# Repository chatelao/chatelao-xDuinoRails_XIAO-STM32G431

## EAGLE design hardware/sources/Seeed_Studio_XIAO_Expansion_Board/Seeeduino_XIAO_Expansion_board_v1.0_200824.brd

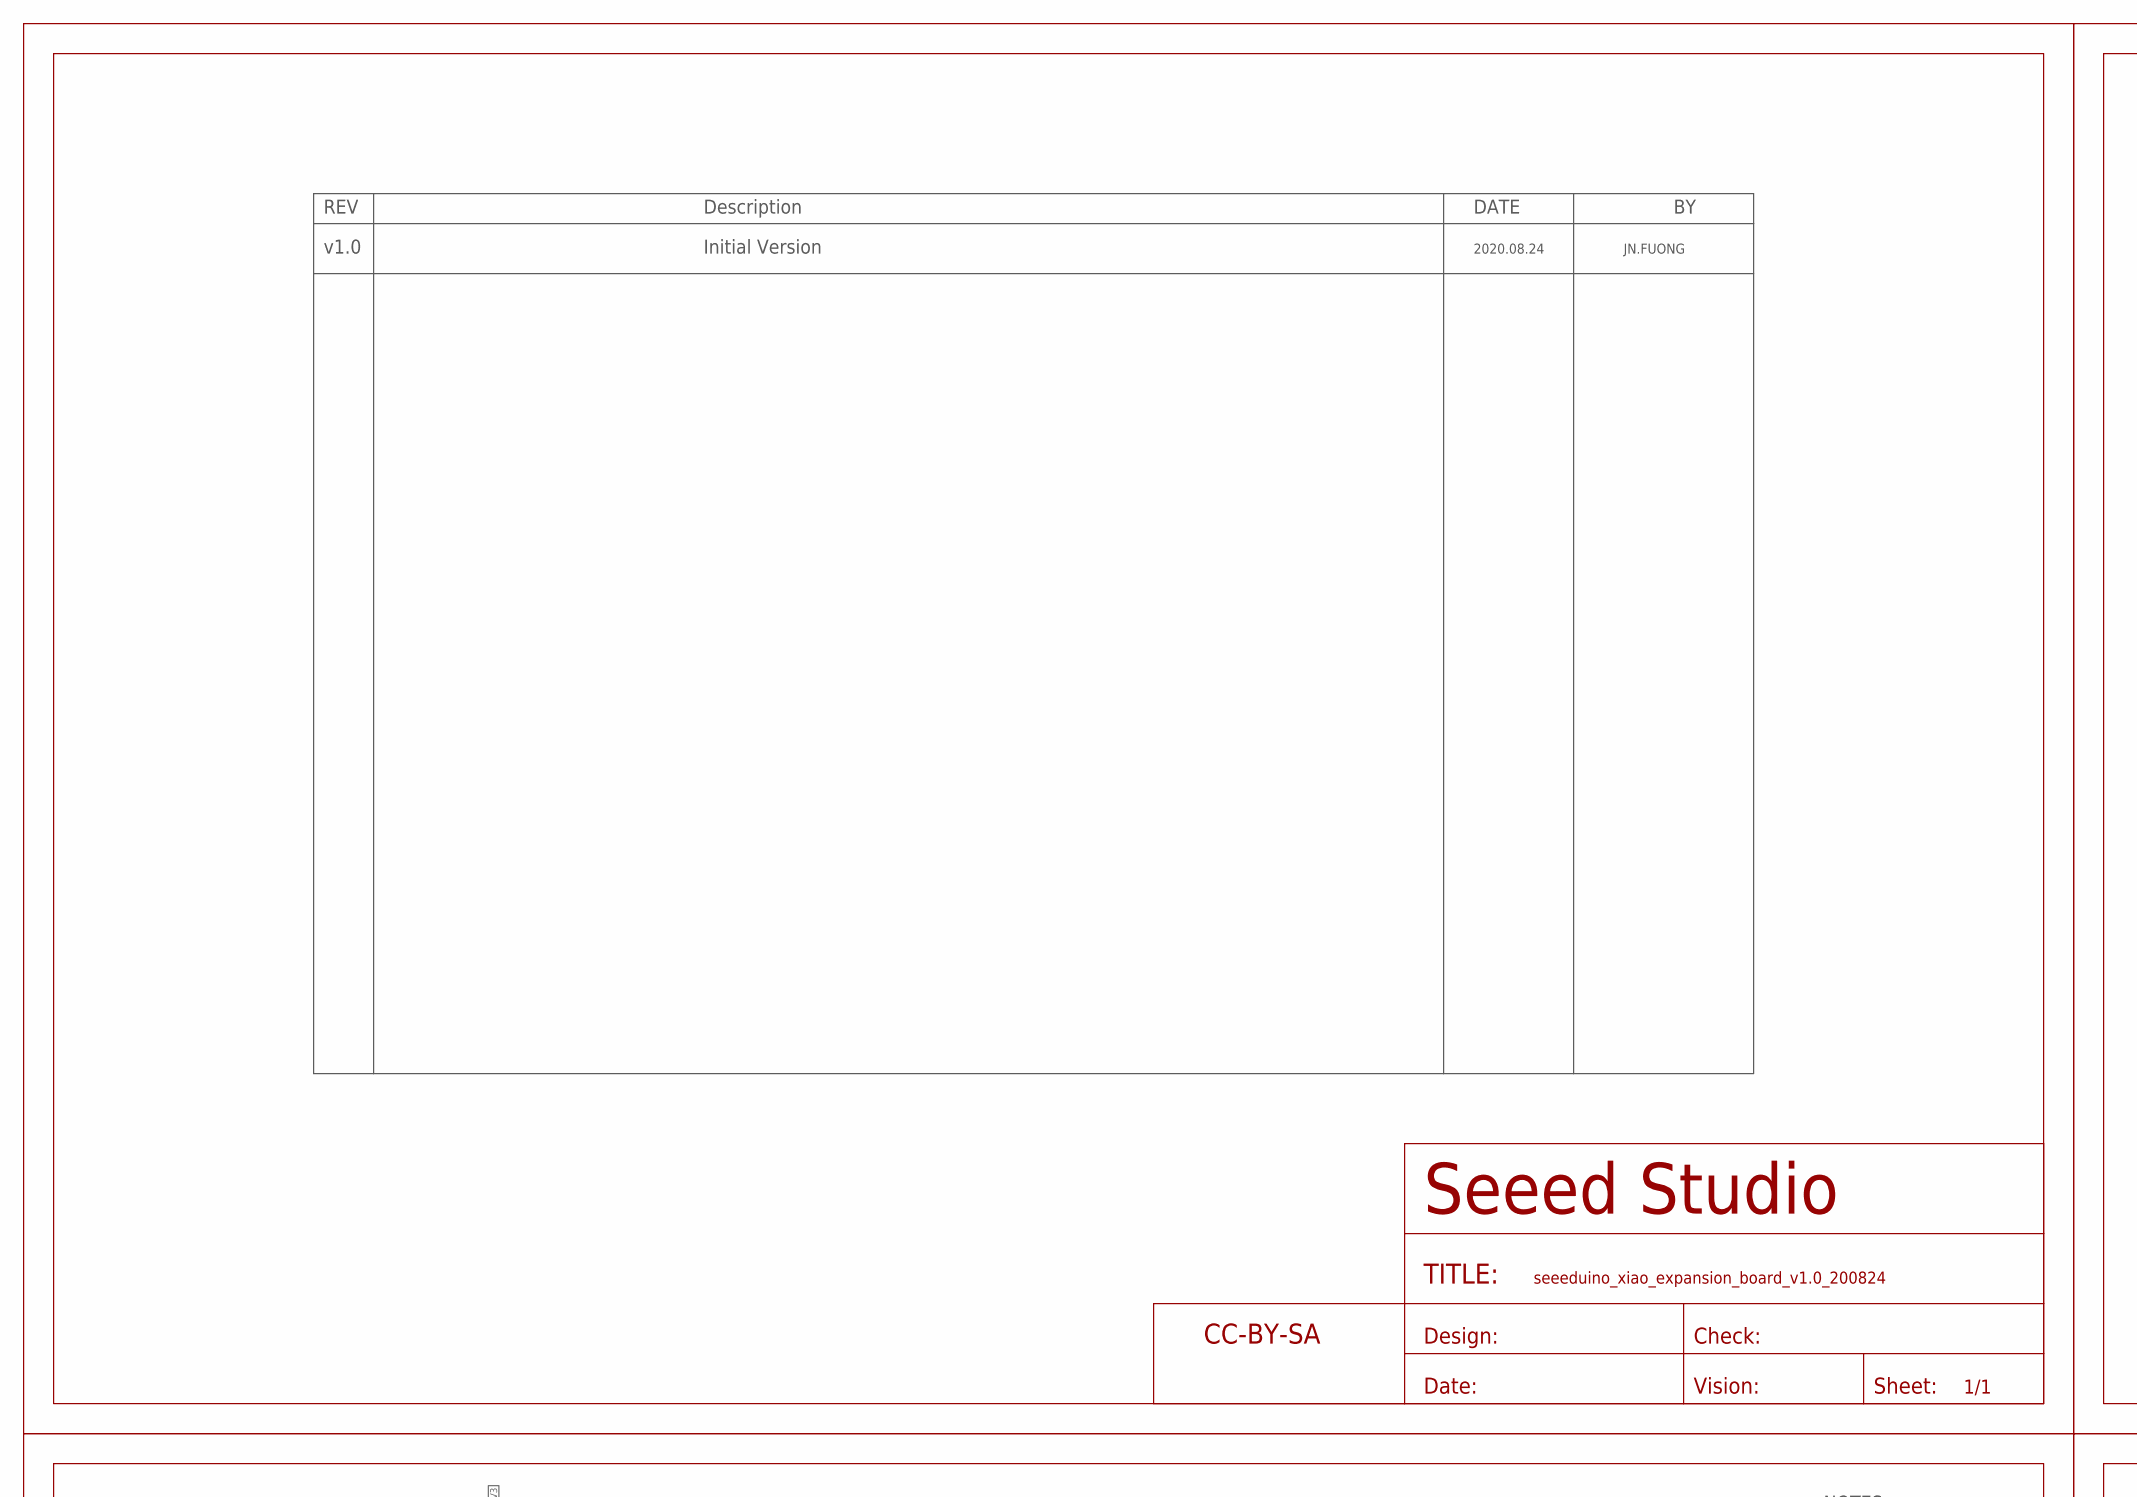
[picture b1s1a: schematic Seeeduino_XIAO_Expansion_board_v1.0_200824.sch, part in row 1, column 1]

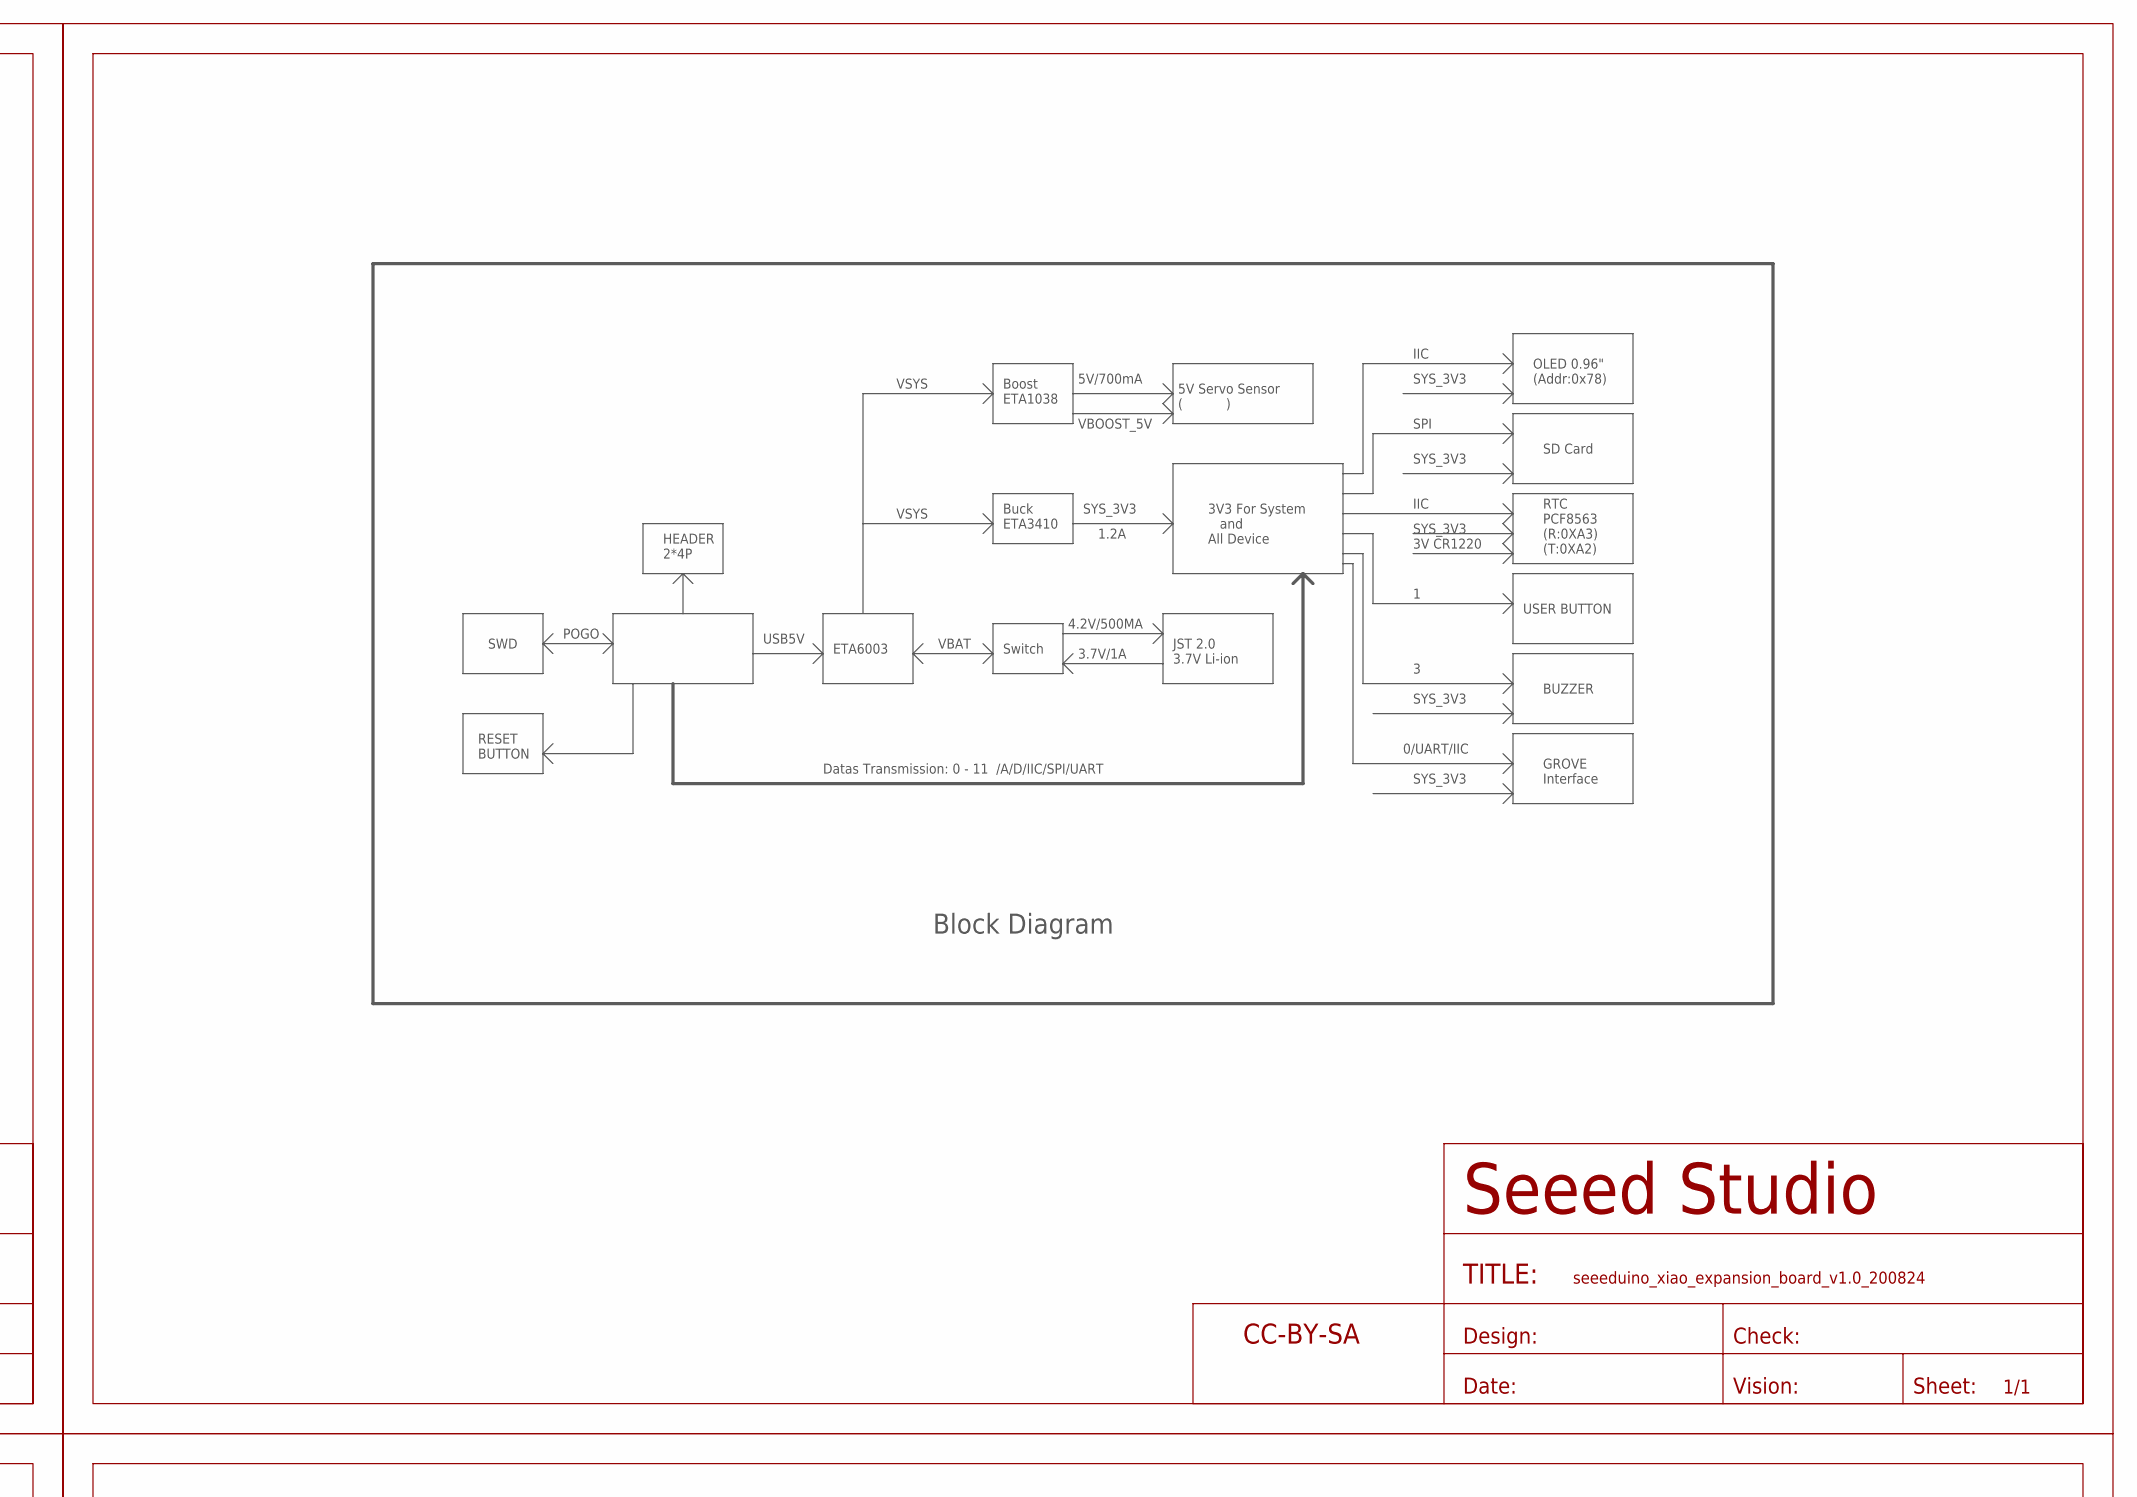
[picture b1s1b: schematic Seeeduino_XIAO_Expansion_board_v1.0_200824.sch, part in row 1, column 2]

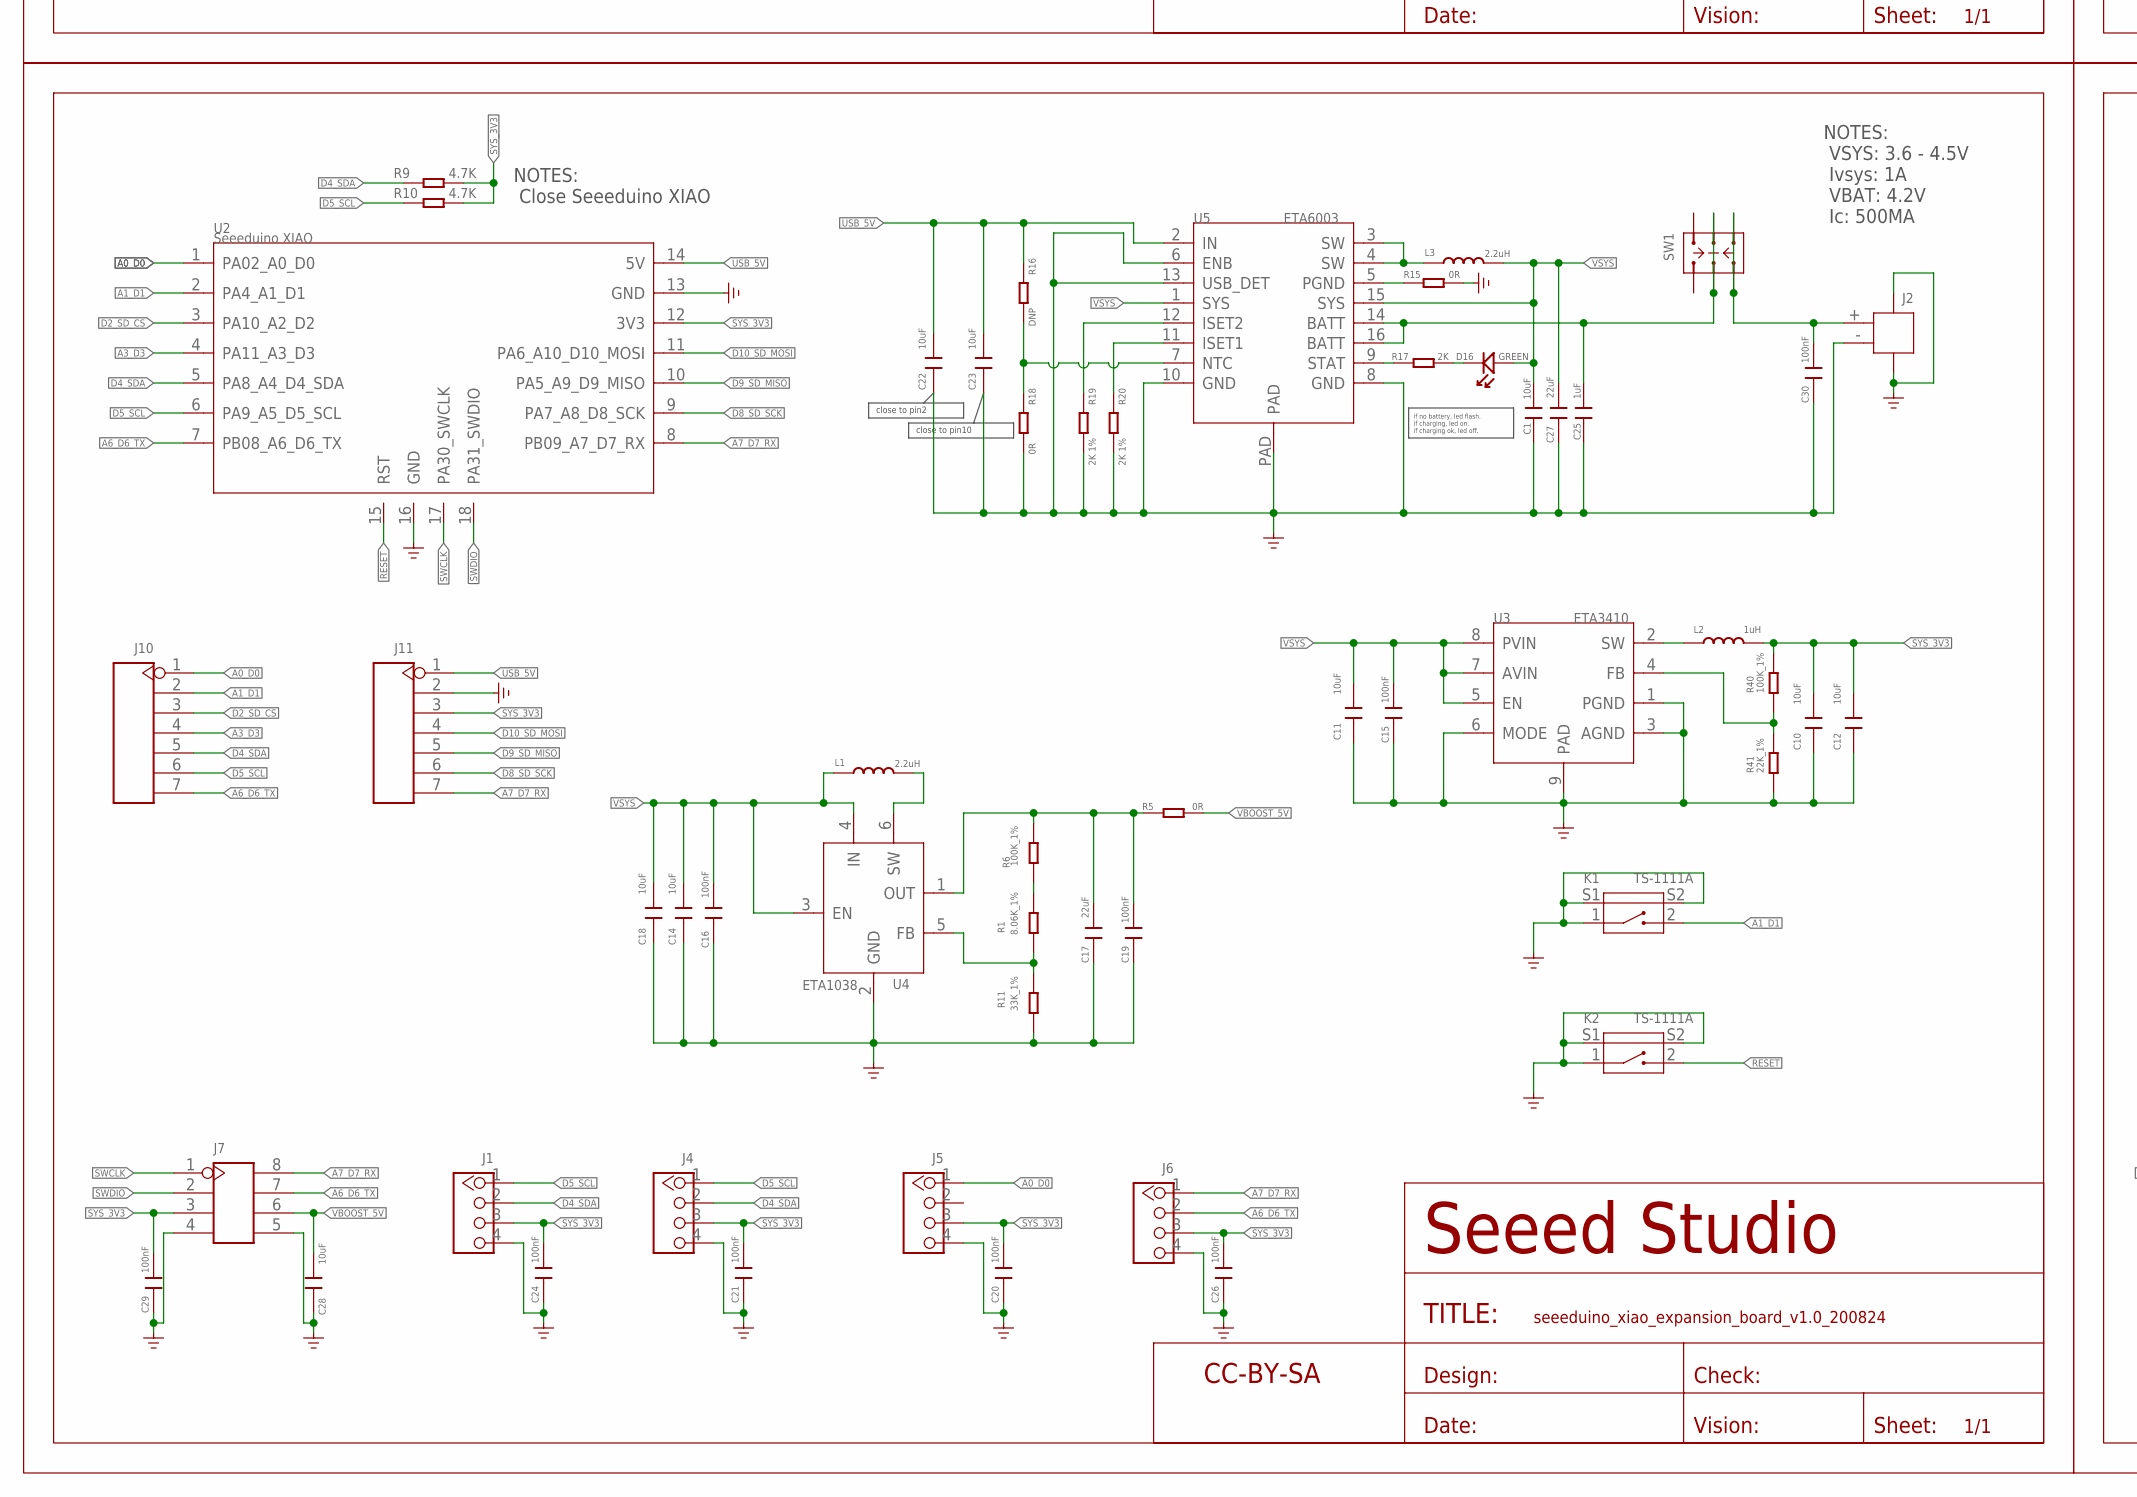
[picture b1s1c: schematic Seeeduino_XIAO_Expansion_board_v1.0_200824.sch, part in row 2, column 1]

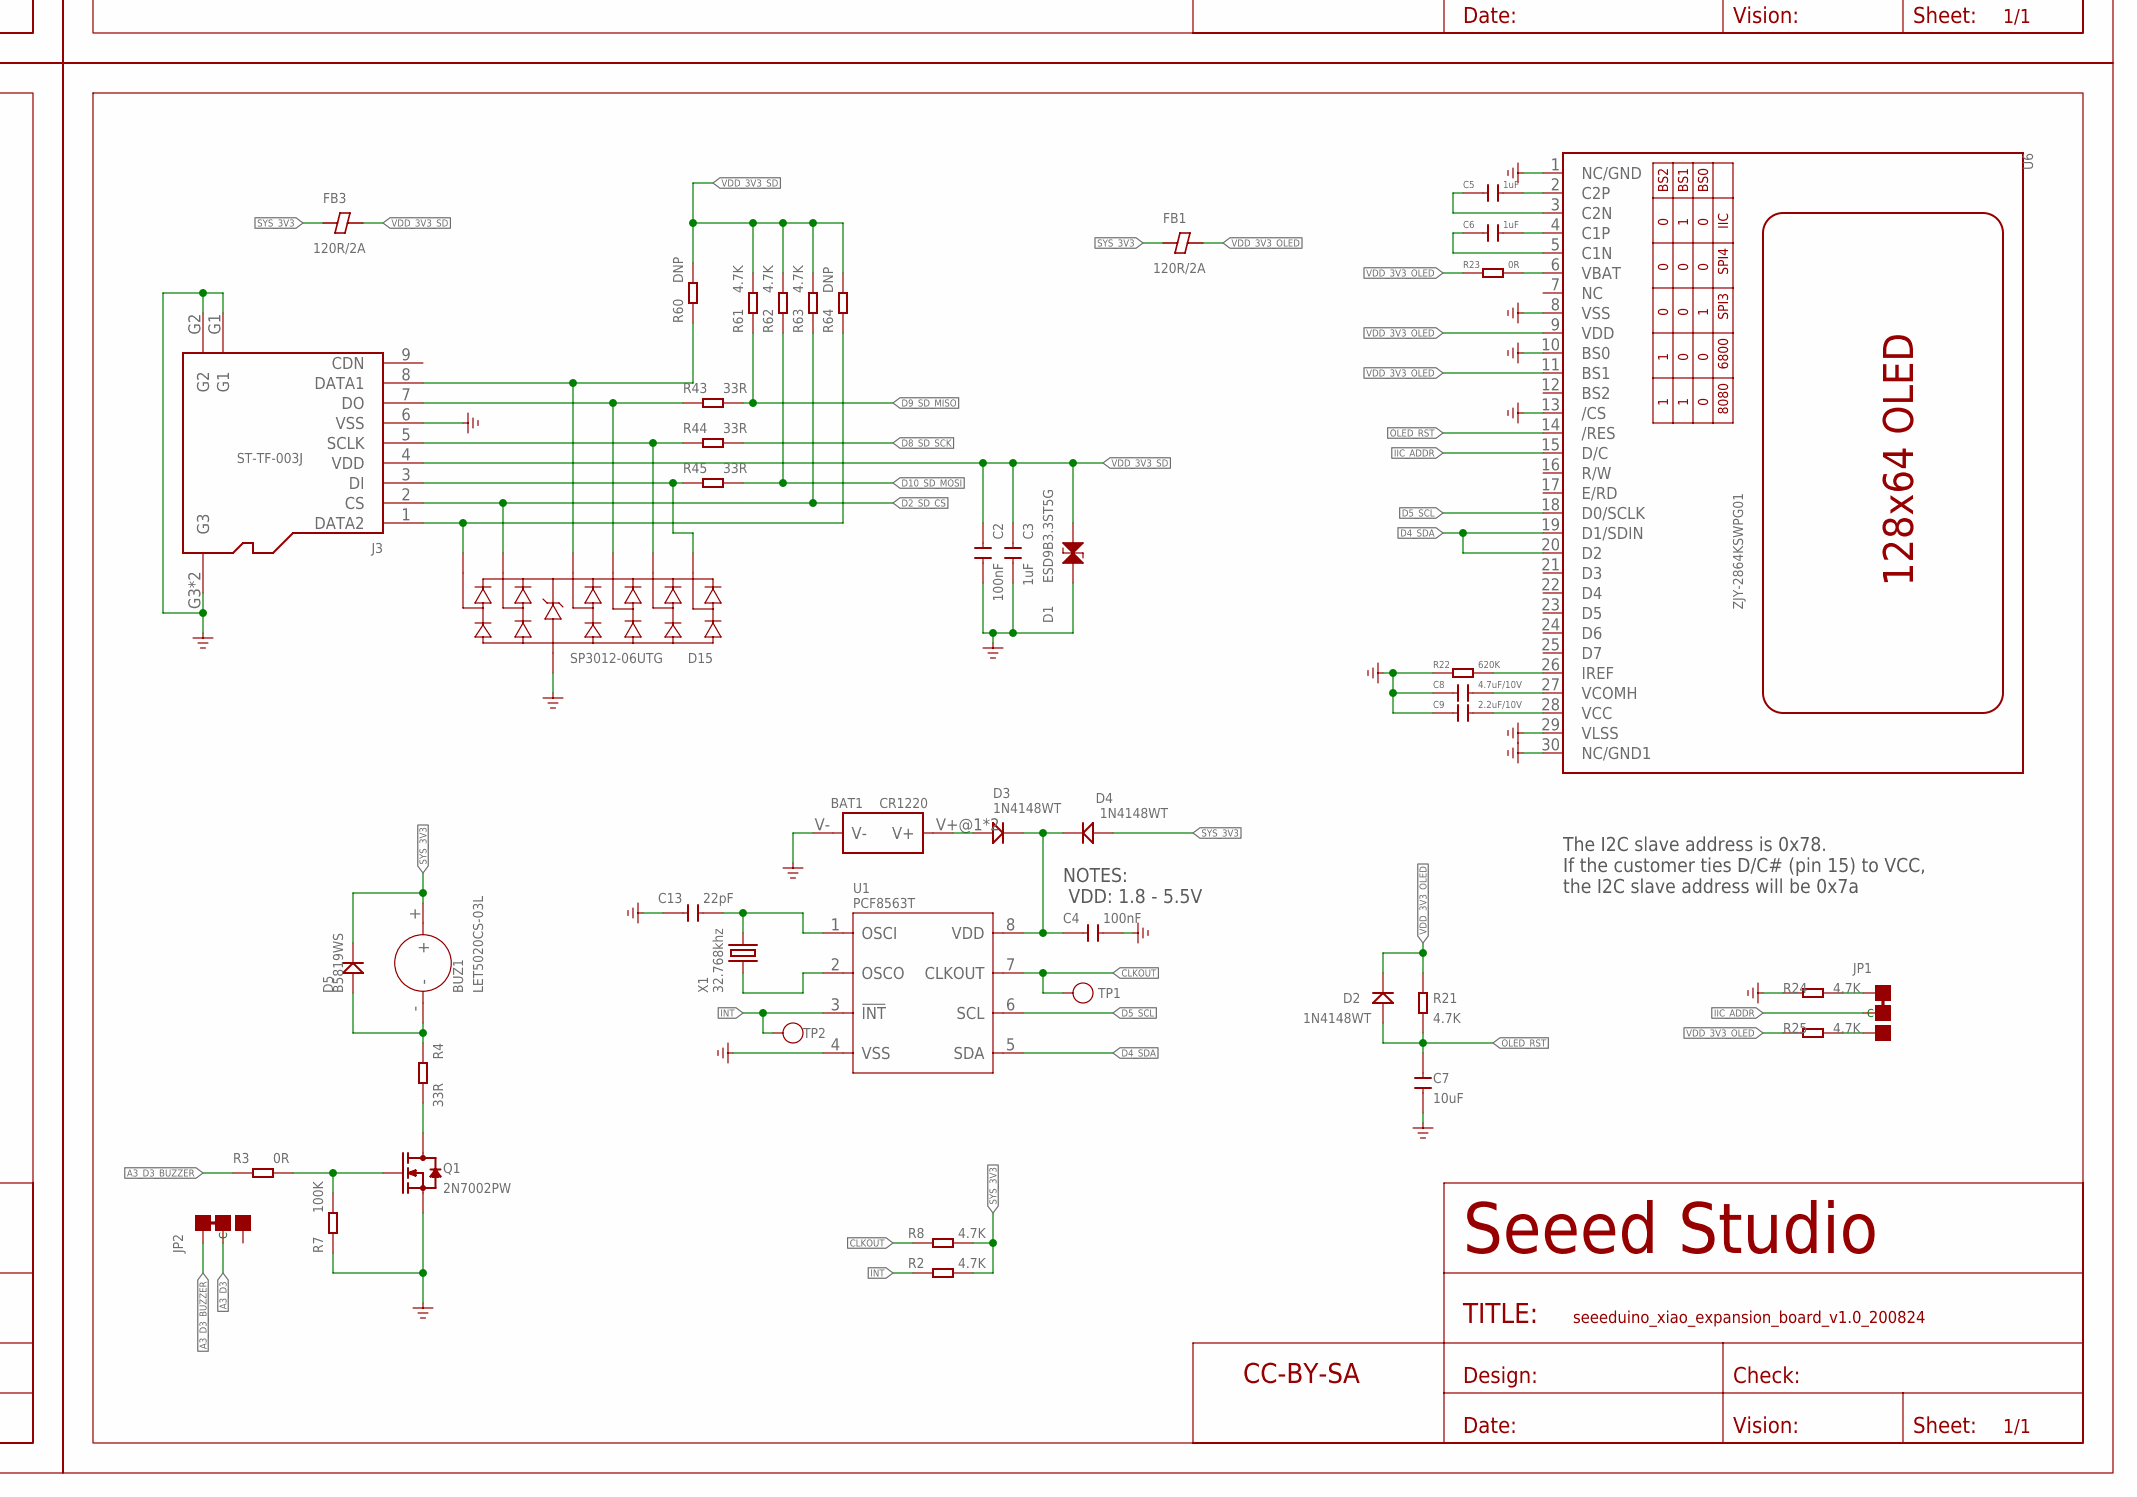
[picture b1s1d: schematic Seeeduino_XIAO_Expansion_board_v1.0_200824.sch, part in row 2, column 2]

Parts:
BAT1: CR1220; BAT2P-SMD-13.2X12.1X3.2MM
BUZ1: LET5020CS-03L; BZ3-SMD-5.0X5.0X2.5MM
C1, C7, C10, C11, C12, C14, C18, C22, C23, C28: 10uF; C0603
C2, C4, C15, C16, C19, C20, C21, C24, C26, C29: 100nF; C0402
C3, C5, C6, C25: 1uF; C0402
C8: 4.7uF/10V; C0603
C9: 2.2uF/10V; C0603
C13: 22pF; C0402
C17, C27: 22uF; C0603
C30: 100nF; C0603
D1: ESD9B3.3ST5G; ESD-0402
D2, D3, D4: 1N4148WT; SOD-523
D5: B5819WS; SOD-323
D15: SP3012-06UTG; UDFN14-0.5-3.5X1.35X0.5MM
D16: GREEN; LED-0402
FB1, FB3: 120R/2A; F0402
FR1, FR2, FR3, FR5: SEEEDSTUDIO-OPEN-SCH-FRAME; SEEEDSTUDIO-PCB-FRAME
J1, J4, J5, J6: GROVE-CONNECTOR-DIP-320110034; HW4-2.0-90D
J2: JST-2P-SMD'2.0'; HW2-SMD-2.0-90D
J3: ST-TF-003J; MICRO-SD9+4P-SMD-16.1X14.5X1.85MM
J7: HEADER-2X4P-2.54-SMD; H2X4-SMD-2.54
J10, J11: HEADER-7P-2.54; H7-2.54
JP1, JP2: JP-3P-SHORT; 3P-SMD-SHORT
K1, K2: TS-1111A; SW4-SMD-4.5X3.8X1.8MM-90D
L1, L3: 2.2uH; L0806
L2: 1uH; L201610
Q1: 2N7002PW; SOT-323
R1: 8.06K_1%; R0402
R2, R8, R9, R10, R21, R24, R25, R61, R62, R63: 4.7K; R0402
R3, R15, R18, R23: 0R; R0402
R4, R43, R44, R45: 33R; R0402
R5: 0R; R0603
R6, R40: 100K_1%; R0402
R7: 100K; R0402
R11: 33K_1%; R0402
R16, R60, R64: DNP; R0402
R17: 2K; R0402
R19, R20: 2K 1%; R0402
R22: 620K; R0402
R41: 22K_1%; R0402
SW1: SWITCH-2CH-6P-311030004; SW6-2.54-9.0X3.5X3.2MM-90D
TP1, TP2: TEST-POINT'4545'; TP-D45MIL
U1: PCF8563T; SOP8-1.27-5X3.9MM
U2: Seeeduino XIAO; MOUDLE14P-2.54-21X17.8MM-TEST
U3: ETA3410; DFN8G-0.5-2X2MM
U4: ETA1038; SOT-23-6
U5: ETA6003; QFN16GA-0.5-3X3MM
U6: ZJY-2864KSWPG01; OLED30P-0.7-24.74X16.9MM
X1: 32.768khz; X2-SMD-L2.0X1.2X0.55MM

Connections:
A0_D0: J5.1, J10.1, U2.1 (PA02_A0_D0)
A1_D1: J10.2, K1.2, U2.2 (PA4_A1_D1)
A3_D3: J10.4, JP2.MM (C), U2.4 (PA11_A3_D3)
A3_D3_BUZZER: JP2.11 (L), R3.1
A6_D6_TX: J6.2, J7.7, J10.7, U2.7 (PB08_A6_D6_TX)
A7_D7_RX: J6.1, J7.8, J11.7, U2.8 (PB09_A7_D7_RX)
CLKOUT: R8.1, TP1.T, U1.7 (CLKOUT)
D2_SD_CS: D15.6 (9), D15.9, J3.2 (CS), J10.3, R63.1, U2.3 (PA10_A2_D2)
D4_SDA: J1.2, J4.2, J10.5, R9.1, U1.5 (SDA), U2.5 (PA8_A4_D4_SDA), U6.19 (D1/SDIN), U6.20 (D2)
D5_SCL: J1.1, J4.1, J10.6, R10.1, U1.6 (SCL), U2.6 (PA9_A5_D5_SCL), U6.18 (D0/SCLK)
D8_SD_SCK: J11.6, R44.2, U2.9 (PA7_A8_D8_SCK)
D9_SD_MISO: J11.5, R43.2, R61.1, U2.10 (PA5_A9_D9_MISO)
D10_SD_MOSI: J11.4, R45.2, R62.1, U2.11 (PA6_A10_D10_MOSI)
E_VBAT: C30.2, J2.+ (1), SW1.CH1B, SW1.CH2B
GND: BAT1.V-, C1.2, C2.2, C3.2, C4.2, C7.2, C8.1, C9.1, C10.2, C11.2, C12.2, C13.1, C14.2, C15.1, C16.1, C17.1, C18.2, C19.1, C20.1, C21.1, C22.2, C23.2, C24.1, C25.2, C26.1, C27.1, C28.2, C29.1, C30.1, D1.1, D15.5 (10), D15.10, J1.4, J2.3, J2.4, J2.- (2), J3.6 (VSS), J3.G1, J3.G2, J3.G3, J3.G4 (G3), J4.4, J5.4, J6.4, J7.4, J7.5, J11.2, K1.1, K1.S1, K1.S2, K2.1, K2.S1, K2.S2, Q1.2 (S), R7.1, R11.2, R15.2, R18.2, R19.2, R20.2, R22.2, R24.1, R41.1, U1.4 (VSS), U2.13 (GND), U2.16 (GND), U3.1 (PGND), U3.3 (AGND), U3.6 (MODE), U3.9 (PAD), U4.2 (GND), U5.6 (ENB), U5.8 (GND), U5.10 (GND), U5.13 (USB_DET), U5.PAD, U6.1 (NC/GND), U6.8 (VSS), U6.10 (BS0), U6.13 (/CS), U6.29 (VLSS), U6.30 (NC/GND1)
IIC_ADDR: JP1.MM (C), U6.15 (D/C)
INT: R2.1, TP2.T, U1.3 (!INT)
unnamed: L1.2, U4.6 (SW)
unnamed: BAT1.V+@1 (V+), BAT1.V+@2 (V+), D3.+
unnamed: Q1.3 (D), R4.2
unnamed: BUZ1.-, D5.+, R4.1
unnamed: Q1.1 (G), R3.2, R7.2
unnamed: C5.2, U6.2 (C2P)
unnamed: C13.2, U1.1 (OSCI), X1.2
unnamed: U1.2 (OSCO), X1.1
unnamed: C6.2, U6.4 (C1P)
unnamed: C5.1, U6.3 (C2N)
unnamed: C6.1, U6.5 (C1N)
unnamed: R22.1, U6.26 (IREF)
unnamed: C8.2, U6.27 (VCOMH)
unnamed: C9.2, U6.28 (VCC)
unnamed: R23.2, U6.6 (VBAT)
unnamed: JP1.11 (L), R24.2
unnamed: JP1.00 (R), R25.2
unnamed: R40.1, R41.2, U3.4 (FB)
unnamed: C17.2, C19.2, R5.2, R6.1, U4.1 (OUT)
unnamed: C4.1, D3.-, D4.-, U1.8 (VDD)
unnamed: R1.1, R6.2
unnamed: L3.1, U5.3 (SW), U5.4 (SW)
unnamed: R1.2, R11.1, U4.5 (FB)
unnamed: L2.1, U3.2 (SW)
unnamed: D16.-, R17.1
unnamed: R17.2, U5.9 (STAT)
unnamed: R16.2, R18.1, U5.7 (NTC)
unnamed: R20.1, U5.11 (ISET1)
unnamed: R19.1, U5.12 (ISET2)
unnamed: R15.1, U5.5 (PGND)
unnamed: D15.1 (14), D15.14, J3.8 (DATA1), R60.1
unnamed: D15.7 (8), D15.8, J3.1 (DATA2), R64.1
unnamed: D15.2 (13), D15.13, J3.7 (DO), R43.1
unnamed: D15.3 (12), D15.12, J3.5 (SCLK), R44.1
unnamed: D15.4 (11), D15.11, J3.3 (DI), R45.1
OLED_RST: C7.1, D2.+, R21.1, U6.14 (/RES)
RESET: K2.2, U2.15 (RST)
SWCLK: J7.1, U2.17 (PA30_SWCLK)
SWDIO: J7.2, U2.18 (PA31_SWDIO)
SYS_3V3: BUZ1.+, C10.1, C12.1, C20.2, C21.2, C24.2, C26.2, C29.2, D4.+, D5.-, FB1.1, FB3.1, J1.3, J4.3, J5.3, J6.3, J7.3, J11.3, L2.2, R2.2, R8.2, R9.2, R10.2, R40.2, U2.12 (3V3)
USB_5V: C22.1, C23.1, J11.1, R16.1, U2.14 (5V), U5.2 (IN)
VBAT: C25.1, SW1.COM1, SW1.COM2, U5.14 (BATT), U5.16 (BATT)
VBOOST_5V: C28.1, J7.6, R5.1
VDD_3V3_OLED: D2.-, FB1.2, R21.2, R23.1, R25.1, U6.9 (VDD), U6.11 (BS1)
VDD_3V3_SD: C2.1, C3.1, D1.2, FB3.2, J3.4 (VDD), R60.2, R61.2, R62.2, R63.2, R64.2
VSYS: C1.1, C11.1, C14.1, C15.2, C16.2, C18.1, C27.2, D16.+, L1.1, L3.2, U3.5 (EN), U3.7 (AVIN), U3.8 (PVIN), U4.3 (EN), U4.4 (IN), U5.1 (SYS), U5.15 (SYS)

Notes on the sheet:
v1.0
Initial Version
2020.08.24
JN.FUONG
close to pin10
if no battery, led flash. if charging, led on. if charging ok, led off.
close to pin2
The I2C slave address is 0x78. If the customer ties D/C# (pin 15) to VCC, the I2C slave address will be 0x7a
ETA6003
USB5V
VSYS
VBAT
Switch
4.2V/500MA
JST 2.0 3.7V Li-ion
3.7V/1A
Buck ETA3410
3V3 For System and All Device
SYS_3V3
Boost ETA1038
5V Servo Sensor ( )
5V/700mA
Datas Transmission: 0 - 11 /A/D/IIC/SPI/UART
OLED 0.96" (Addr:0x78)
IIC
SD Card
RTC PCF8563 (R:0XA3) (T:0XA2)
SPI
USER BUTTON
BUZZER
GROVE Interface
HEADER 2*4P
SWD
POGO
0/UART/IIC
RESET BUTTON
VBOOST_5V
3V CR1220
1.2A
Block Diagram

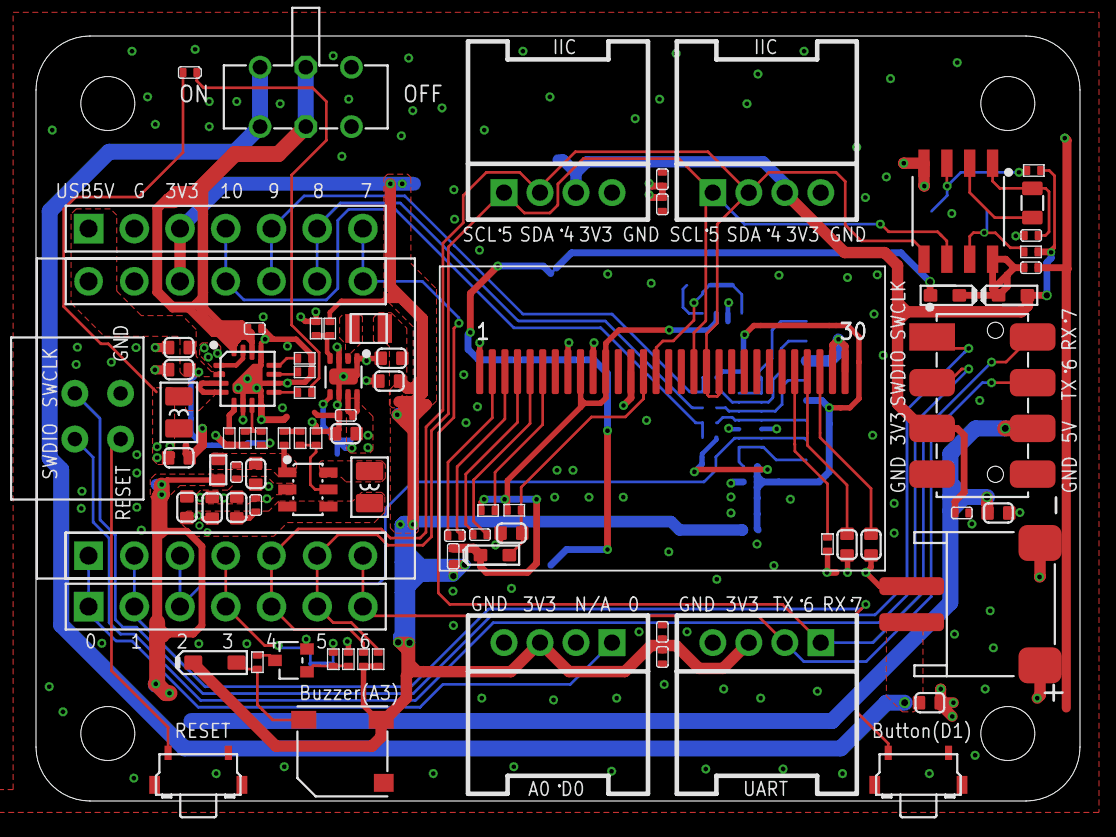
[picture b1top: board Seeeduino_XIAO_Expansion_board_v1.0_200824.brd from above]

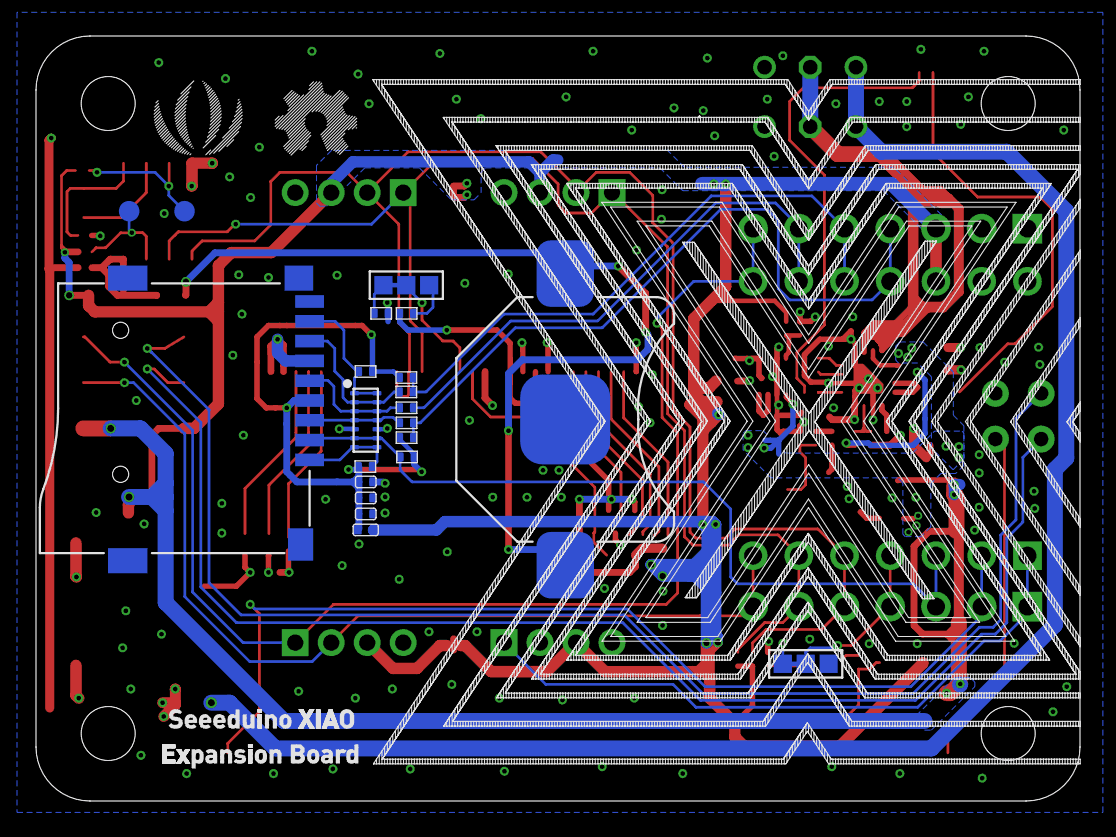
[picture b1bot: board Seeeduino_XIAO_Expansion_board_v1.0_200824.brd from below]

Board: 2 copper layers, 58.0 x 42.5 mm, 104 parts (21 on the bottom side), 63 nets.

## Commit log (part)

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2025-11-28 Add schematic for Xiao STM32G431
2025-11-28 Import netlist to KiCad schematic
    Created a python script `hardware/netlist_to_sch.py` to convert a KiCad netlist file (`.net`) into a KiCad schematic file (`.kicad_sch`).
    The script parses the netlist to extract components and their connections, then generates a schematic with embedded symbol definitions.
    Symbols are generated as rectangular boxes with pins, placed in a grid layout.
    Connections are established using wires and net labels attached to pins.
    Generated `hardware/xiao_stm32g431_imported.kicad_sch` from `hardware/xiao_stm32g431.net` as a result.
2025-11-30 Add implementation roadmap for JLCPCB manufacturing
    Added a ROADMAP.md file outlining the steps for schematic design, PCB layout, manufacturing preparation, and ordering at JLCPCB for the XIAO STM32G431 project.
2025-11-30 feat: add XIAO STM32G431 pin mapping documentation
    This commit adds a detailed pinout mapping table (`XIAO_STM32G431_Pinout.md`) for a Seeed Studio XIAO compatible board using the STM32G431CBU6 microcontroller.
    The mapping prioritizes:
    - **Legacy Compatibility:** Matches XIAO RP2040/SAMD21 functions for D0-D10 (Analog, I2C, UART, SPI).
    - **Extended Features:** Exposes SPI2, UART3, and extra Analog inputs via bottom pads.
    - **Robustness:** Avoids BOOT0 (PB8) conflicts on I2C lines by using PA15 for SCL.
2025-11-30 Add Seeed Studio XIAO nRF52840 Plus KiCad files
    Downloaded and extracted the KiCad project files for the Seeed Studio XIAO nRF52840 Plus board into the `seeed/` directory.
    - Source: Seeed Studio Wiki (Seeed_Studio_XIAO_nRF52840_Plus.zip)
    - Files included: .kicad_pro, .kicad_sch, .kicad_pcb, .kicad_prl
2025-11-30 Add partlist and design comparison for XIAO STM32G431
    - Create `hardware/PARTLIST.md` with components derived from netlist.
    - Add "Design Choices & Comparison" section comparing features with XIAO SAMD21 and RP2040.
    - Update `ROADMAP.md` to reference the new partlist.
    - Include RGB LED in partlist to match modern XIAO standards.
2025-11-30 Propose pinout mapping for XIAO STM32G431.
    This proposal outlines the pin assignments for the STM32G431KBU6 on a
    XIAO form factor. It prioritizes compatibility with standard XIAO functions
    (DAC on D0, I2C, SPI, UART) and addresses package constraints (unavailable PB2).
    Key Features:
    - D0 mapped to PA4 for DAC support.
    - Standard interfaces (I2C1, SPI1, USART1) on expected pins.
2025-11-30 Add minimalistic MicroPython build for XIAO STM32G431
    - Create `micropython/` directory with board definition for XIAO_STM32G431.
    - Configure board for 128KB flash (STM32G431KBU6) with minimal features (disabled AsyncIO, Network, etc.).
    - Set up build script `build_firmware.sh` to clone and build MicroPython.
    - Add GitHub Actions workflow `build_micropython.yml` for CI/CD and release publishing.
    - Configure clock to use HSI (16MHz) for system and HSI48 for USB.
2025-11-30 Finalize XIAO STM32G431 Pinout Proposal.
    This update finalizes the pin mapping documentation (`PINOUT_PROPOSAL.md`)
    based on detailed analysis of the STM32G431KBU6 datasheet and user requirements.
    Key Changes:
    - **NeoPixel**: Assigned to PB0 (TIM3_CH3) for PWM/DMA control, replacing discrete RGB LEDs.
    - **Analog**: Comprehensive mapping of COMP and OPAMP peripherals.
    - Correctly identifies OPAMP1 input/output pins to confirm standalone mode capability (VINM on P0/PA3).
2025-11-30 Fix GitHub Actions workflow for MicroPython build
    - Replace broken `resetlabs/setup-arm-none-eabi-gcc` action with `sudo apt-get install gcc-arm-none-eabi`.
    - Upgrade `actions/upload-artifact` to v4 to fix deprecation warning.
    - Upgrade `actions/checkout` to v4.
    - Use `softprops/action-gh-release` instead of deprecated `actions/upload-release-asset`.
2025-12-01 Fix MicroPython build errors and runtime stability - Added missing `stm32g4xx_hal_conf.h` to board directory. - Updated `mpconfigboard.h` to use correct `FLASH_LATENCY_8` for 170MHz clock to prevent 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
2025-12-01 Add Arduino examples for STM32G4 OpAmp, Comparator, and CORDIC
    Added three Arduino sketches in `software/examples/` demonstrating advanced hardware features of the STM32G431:
    1. `STM32G4_OpAmp_Buffer`: Configures internal OpAmp1 as a voltage follower (D2 -> D3).
    2. `STM32G4_Comparator_DAC`: Configures internal COMP1 with DAC1 reference (D2 vs 1.65V -> D9).
    3. `STM32G4_CORDIC_SinCos`: Demonstrates CORDIC hardware accelerator for high-speed trigonometry.
2025-12-01 Add AGENTS.md with roadmap instructions
    Added AGENTS.md to the root directory with instructions for agents to:
    1. Read ROADMAP.md before every task.
    2. Update ROADMAP.md at the end of every task.
2025-12-01 Add reference designs for XIAO and QT Py boards
    Created `hardware/sources` and added:
    - Seeed Studio XIAO nRF52840 (KiCad files copied from `seeed/`)
    - Seeed Studio XIAO Expansion Board (Eagle files downloaded from Wiki)
    - Adafruit QT Py RP2040 (Eagle/KiCad files cloned from GitHub)
    These examples serve as references for the XIAO STM32G431 design.
2025-12-01 Fix MicroPython build for 128KB STM32G431
    - Explicitly disable floating point support in mpconfigboard.h and mpconfigboard.mk
    - Create minimal manifest.py to exclude standard frozen modules (e.g. dht) that require floats
    - Update build configuration to ensure firmware fits in 128KB flash
    - Fix linker script usage and HAL configuration paths
2025-12-01 Add documentation index with manuals and application notes
    Created DOCUMENTATION.md containing links to:
    - Official STM32G431 Datasheet, Reference Manual (RM0440), and Errata (ES0431).
    - Application notes for Analog features (OpAmp, Comparator, DAC).
    - Application notes for Coprocessors (CORDIC, FMAC).
2025-12-01 Fix MicroPython build errors by updating linker script and disabling unused features
    - Changed `mpconfigboard.mk` to use `boards/common.ld` instead of `boards/common_basic.ld` which does not exist.
    - Updated `mpconfigboard.h` to disable `MICROPY_HW_ENABLE_INTERNAL_FLASH_STORAGE` to prevent linker errors on 128KB flash.
    - Explicitly disabled `MICROPY_PY_MACHINE_IDLE` and `MICROPY_PY_LWIP` to resolve "used but never defined" errors in `modmachine.c`.
    - Confirmed minimal build settings for STM32G431KBU6 (128KB Flash).
2025-12-01 Fix MicroPython build errors by undefining unused machine features and adding pins.csv
    - Explicitly `#undef` `MICROPY_PY_MACHINE_IDLE`, `MICROPY_PY_MACHINE_PULSE`, and `MICROPY_PY_LWIP` in `mpconfigboard.h` before setting them to 0. This resolves the "used but never defined" compilatio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
    - Added `pins.csv` mapping standard XIAO pins (D0-D10) and system pins (USB, SWD, LED) for the STM32G431.
    - Ensured `manifest.py` is present (empty) to avoid freezing modules that require floats.
    - Confirmed minimal build settings for 128KB Flash target.
2025-12-02 Fix netlist to align with Pinout Proposal and Standard XIAO Layout
    - Update `hardware/xiao_stm32g431.net`:
    - Re-map U1 (STM32G431KBU6) pins to match `XIAO_STM32G431_Pinout.md` as closely as possible within 32-pin constraints.
    - D0=PA4, D1=PA0, D2=PA1, D3=PA2.
    - Correct PA15 assignment (Pin 25).
    - Reorder J3 header pins to match Standard XIAO (5V, GND, 3V3, D10, D9, D8, D7).
    - Map D10 to PA7 and connect to J3 Pin 4.
2025-12-02 Fix MicroPython build: Enable MACHINE_IDLE correctly
    Updated mpconfigboard.h and mpconfigboard.mk to explicitly disable
    MICROPY_PY_MACHINE_IDLE via CFLAGS to resolve the "used but never defined"
    error in modmachine.c. Provided build scripts and workflows.
2025-12-02 Fix MicroPython build: Correctly disable MACHINE_IDLE
    Restored `MICROPY_PY_MACHINE_IDLE = 0` as a Make variable in `mpconfigboard.mk`
    alongside the `CFLAGS` override. This ensures the build system correctly
    generates the flags to disable the idle function, preventing the
    "used but never defined" compilation error. Verified pin mappings against
    project netlist.
2025-12-06 Add STM32G4 FMAC and CORDIC examples
    Added two new Arduino sketches to the `software/examples` directory:
    - `STM32G4_FMAC_FIR`: Demonstrates using the FMAC peripheral for a 7-tap FIR filter in polling mode.
    - `STM32G4_CORDIC_Polar`: Demonstrates using the CORDIC peripheral for Cartesian-to-Polar conversion (Modulus/Phase).
    Verified FMAC HAL usage against the stm32g4xx_hal_driver headers.
2025-12-06 Add GitHub Actions workflow for Arduino builds
    Created .github/workflows/arduino_build.yml to:
    - Compile all sketches in software/examples/ on every push.
    - Use STM32duino Core with Generic G431KBUx configuration.
    - Publish compiled .hex files as artifacts on every build.
    - Upload .hex files to Release assets when a release is published.
2025-12-06 Update GitHub Actions to v4 to fix deprecation error
    Updated actions/checkout and actions/upload-artifact to v4 in .github/workflows/arduino_build.yml.
    This resolves the build failure caused by the deprecation of node16 runtime in v3 actions.
2025-12-06 Fix Arduino build by enabling HAL modules and correcting CORDIC scaling
    - Added `hal_conf_extra.h` to all example sketches to explicitly enable required HAL modules (CORDIC, FMAC, OPAMP, COMP, DAC) which are disabled by default in Generic STM32G4 variants.
    - Fixed CORDIC Polar example to use a smaller input radius (0.5 instead of 0.8) to prevent q1.31 overflow caused by the CORDIC algorithm's intrinsic gain (~1.647).
2025-12-06 Add STM32G4 FMAC FIR and CORDIC Polar Arduino examples
    This commit adds two new Arduino examples to the software/examples directory:
    1. STM32G4_FMAC_FIR: Demonstrates how to use the FMAC hardware accelerator for FIR filtering in polling mode using q1.15 fixed-point format.
    2. STM32G4_CORDIC_Polar: Demonstrates how to use the CORDIC hardware accelerator for Rectangular-to-Polar conversion, including necessary scaling to handle the intrinsic gain of the Modulus function.
    These examples complement the existing OpAmp, Comparator/DAC, and CORDIC SinCos examples.
2025-12-06 Add GitHub Actions workflow for Arduino builds
    This commit adds a new GitHub Actions workflow `.github/workflows/arduino_build.yml` to automatically compile the Arduino examples on every push to any branch and on pull requests.
    The workflow:
    - Installs Arduino CLI and the STM32 core.
    - Compiles all sketches in `software/examples/` using the FQBN `STMicroelectronics:stm32:GenG4:pnum=GENERIC_G431KBUX,usb=CDCgen`.
    This ensures that all examples remain compatible with the STM32G4 configuration.
    Also updated `ROADMAP.md` to reflect the addition of CI/CD.
2025-12-06 Add hal_conf_extra.h to enable HAL modules in Arduino examples
    This commit fixes build errors in the Arduino examples caused by missing HAL module definitions.
    The STM32duino core does not enable all HAL modules (CORDIC, FMAC, OpAmp, DAC, COMP) by default to save flash.
    We add `hal_conf_extra.h` to each example directory to explicitly enable the required modules:
    - STM32G4_CORDIC_Polar: Enables CORDIC
    - STM32G4_CORDIC_SinCos: Enables CORDIC
    - STM32G4_FMAC_FIR: Enables FMAC
2025-12-07 Finalize Arduino examples and CI with build fixes
    This commit bundles the following changes:
    - New `STM32G4_FMAC_FIR` and `STM32G4_CORDIC_Polar` examples.
    - New `.github/workflows/arduino_build.yml` for CI.
    - `hal_conf_extra.h` files added to all examples to enable required HAL modules.
    - Updated `ROADMAP.md`.
    This ensures the repository has a working set of advanced hardware examples and a CI pipeline to verify them.

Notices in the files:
parts and their libraries:
moudle-new: This work is licensed under the Creative Commons Attribution 4.0 International License.
To view a copy of this license,visit:
http://creativecommons.org/licenses/by-sa/4.0
moudle-new: CC-BY-SA
